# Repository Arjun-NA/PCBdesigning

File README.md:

# PCBdesigning

This is a repository of PCB designs

Currently the following

  1. [8x8 LED matrix control board](led%20matrix%20adapter%208x8%20rgb)
  2. [Breaker board for TLC 5951](/breaker%20board%20for%20tlc5951/)

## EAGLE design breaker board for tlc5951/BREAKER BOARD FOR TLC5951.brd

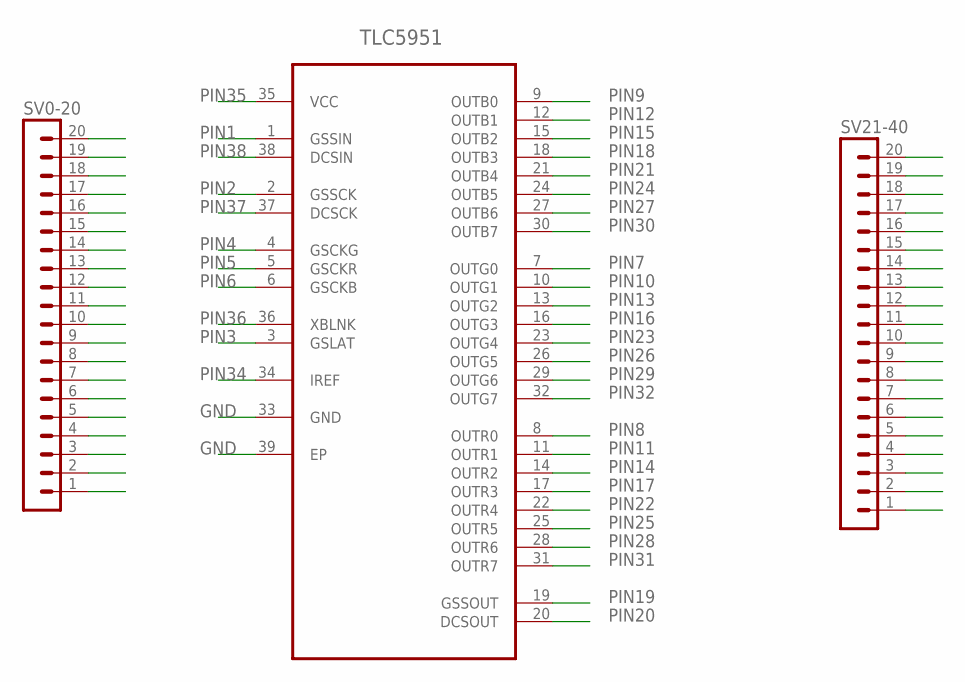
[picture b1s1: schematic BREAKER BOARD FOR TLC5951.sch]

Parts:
SV0-20, SV21-40: MA20-1
TLC5951: TLC5951DAP; SOP65P810X120-39N

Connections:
PIN1: SV0-20.1, TLC5951.1 (GSSIN)
PIN2: SV0-20.2, TLC5951.2 (GSSCK)
PIN3: SV0-20.3, TLC5951.3 (GSLAT)
PIN4: SV0-20.4, TLC5951.4 (GSCKG)
PIN5: SV0-20.5, TLC5951.5 (GSCKR)
PIN6: SV0-20.6, TLC5951.6 (GSCKB)
PIN7: SV0-20.7, TLC5951.7 (OUTG0)
PIN8: SV0-20.8, TLC5951.8 (OUTR0)
PIN9: SV0-20.9, TLC5951.9 (OUTB0)
PIN10: SV0-20.10, TLC5951.10 (OUTG1)
PIN11: SV0-20.11, TLC5951.11 (OUTR1)
PIN12: SV0-20.12, TLC5951.12 (OUTB1)
PIN13: SV0-20.13, TLC5951.13 (OUTG2)
PIN14: SV0-20.14, TLC5951.14 (OUTR2)
PIN15: SV0-20.15, TLC5951.15 (OUTB2)
PIN16: SV0-20.16, TLC5951.16 (OUTG3)
PIN17: SV0-20.17, TLC5951.17 (OUTR3)
PIN18: SV0-20.18, TLC5951.18 (OUTB3)
PIN19: SV0-20.19, TLC5951.19 (GSSOUT)
PIN20: SV21-40.19, TLC5951.20 (DCSOUT)
PIN21: SV21-40.18, TLC5951.21 (OUTB4)
PIN22: SV21-40.17, TLC5951.22 (OUTR4)
PIN23: SV21-40.16, TLC5951.23 (OUTG4)
PIN24: SV21-40.15, TLC5951.24 (OUTB5)
PIN25: SV21-40.14, TLC5951.25 (OUTR5)
PIN26: SV21-40.13, TLC5951.26 (OUTG5)
PIN27: SV21-40.12, TLC5951.27 (OUTB6)
PIN28: SV21-40.11, TLC5951.28 (OUTR6)
PIN29: SV21-40.10, TLC5951.29 (OUTG6)
PIN30: SV21-40.9, TLC5951.30 (OUTB7)
PIN31: SV21-40.8, TLC5951.31 (OUTR7)
PIN32: SV21-40.7, TLC5951.32 (OUTG7)
PIN34: SV21-40.5, TLC5951.34 (IREF)
PIN35: SV21-40.4, TLC5951.35 (VCC)
PIN36: SV21-40.3, TLC5951.36 (XBLNK)
PIN37: SV21-40.2, TLC5951.37 (DCSCK)
PIN38: SV21-40.1, TLC5951.38 (DCSIN)
PIN40: SV21-40.20

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
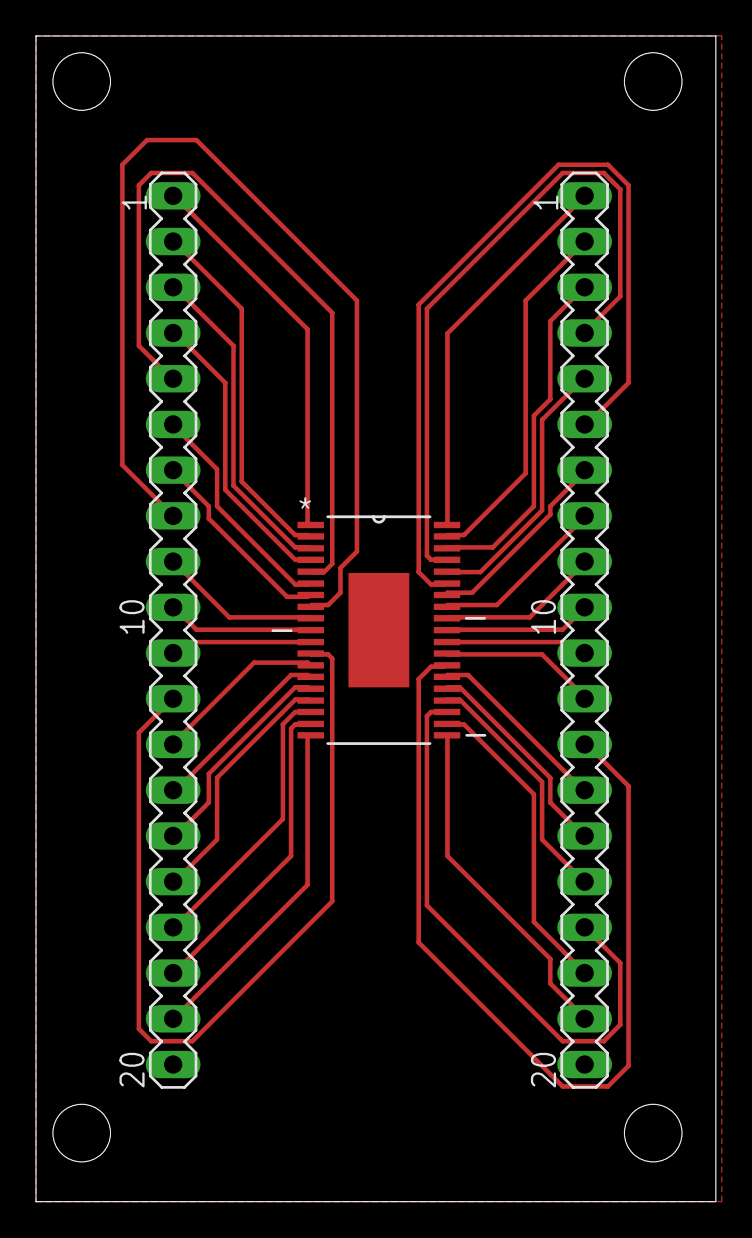
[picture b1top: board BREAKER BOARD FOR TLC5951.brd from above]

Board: 2 copper layers, 37.8 x 64.8 mm, 3 parts (0 on the bottom side), 38 nets.

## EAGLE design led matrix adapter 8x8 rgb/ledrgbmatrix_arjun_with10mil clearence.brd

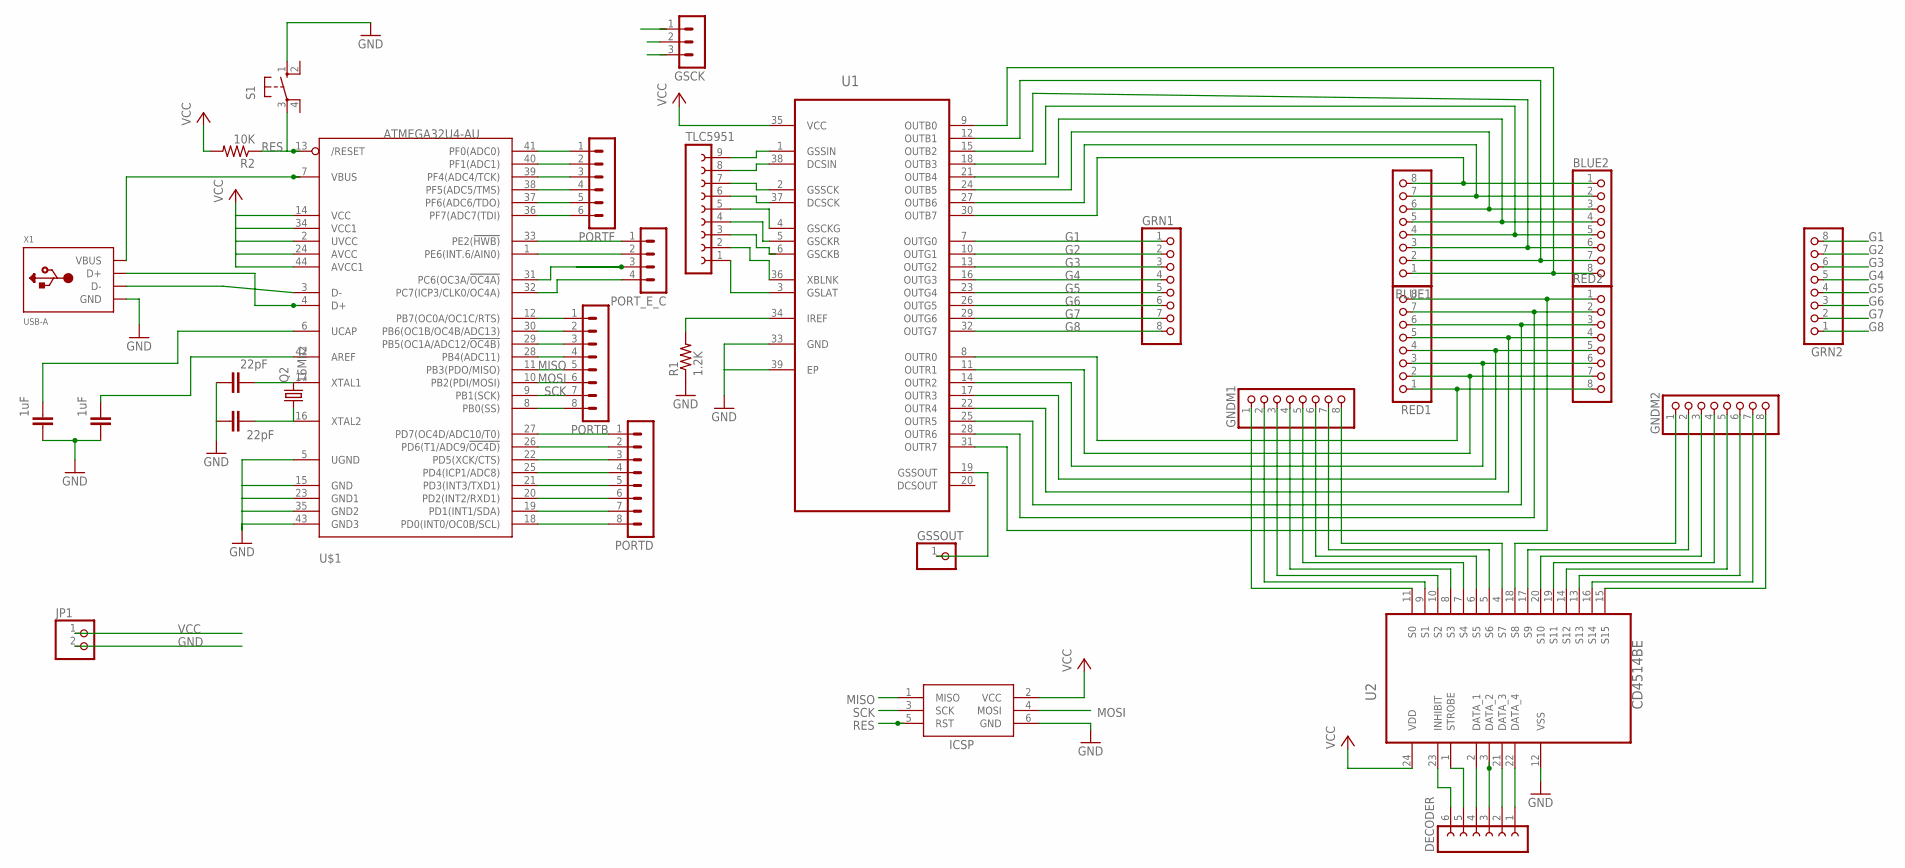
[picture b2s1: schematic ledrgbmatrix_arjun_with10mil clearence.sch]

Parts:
BLUE1, BLUE2: PINHD-1X8BIG; 1X08-BIG
C1, C2: 1uF; C2.5-2
C3, C4: 22pF; C2.5-2
DECODER: FE06-1; FE06
GNDM1, GNDM2: PINHD-1X8BIG; 1X08-BIG
GRN1, GRN2: PINHD-1X8BIG; 1X08-BIG
GSCK: MA03-1
GSSOUT: PINHD-1X1; 1X01
ICSP: AVRISP-6; AVRISP
JP1: PINHD-1X2; 1X02
PORTB: MA08-1
PORTD: MA08-1
PORTF: MA06-1
PORT_E_C: MA04-1
Q2: 16Mhz; HC49U-V
R1: 1.2K; 0207/12
R2: 10K; 0207/12
RED1, RED2: PINHD-1X8BIG; 1X08-BIG
S1: 10-XX; B3F-10XX
TLC5951: FE09-1; FE09
U1: TLC5951DAP; SOP65P810X120-39N
U2: CD4514BE; DIP254P1080X508-24
U$1: ATMEGA32U4-AU; TQFP44
X1: USB-A; MOLEX_480371000

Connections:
AREF: C1.2, U$1.42 (AREF)
B1: BLUE1.1, BLUE2.8, U1.9 (OUTB0)
B2: BLUE1.2, BLUE2.7, U1.12 (OUTB1)
B3: BLUE1.3, BLUE2.6, U1.15 (OUTB2)
B4: BLUE1.4, BLUE2.5, U1.18 (OUTB3)
B5: BLUE1.5, BLUE2.4, U1.21 (OUTB4)
B6: BLUE1.6, BLUE2.3, U1.24 (OUTB5)
B7: BLUE1.7, BLUE2.2, U1.27 (OUTB6)
B8: BLUE1.8, BLUE2.1, U1.30 (OUTB7)
C0: GNDM1.1, U2.11 (S0)
C1: GNDM1.2, U2.9 (S1)
C2: GNDM1.3, U2.10 (S2)
C3: GNDM1.4, U2.8 (S3)
C4: GNDM1.5, U2.7 (S4)
C5: GNDM1.6, U2.6 (S5)
C6: GNDM1.7, U2.5 (S6)
C7: GNDM1.8, U2.4 (S7)
C8: GNDM2.1, U2.18 (S8)
C9: GNDM2.2, U2.17 (S9)
C10: GNDM2.3, U2.20 (S10)
C11: GNDM2.4, U2.19 (S11)
C12: GNDM2.5, U2.14 (S12)
C13: GNDM2.6, U2.13 (S13)
C14: GNDM2.7, U2.16 (S14)
C15: GNDM2.8, U2.15 (S15)
D1: DECODER.4, U2.2 (DATA_1)
D2: DECODER.3, U2.3 (DATA_2)
D3: DECODER.2, U2.21 (DATA_3)
D4: DECODER.1, U2.22 (DATA_4)
D+: U$1.4 (D+), X1.3 (D+)
D-: U$1.3 (D-), X1.2 (D-)
DCSCK: TLC5951.6, U1.37 (DCSCK)
DSCIN: TLC5951.8, U1.38 (DCSIN)
G1: GRN1.1, GRN2.8, U1.7 (OUTG0)
G2: GRN1.2, GRN2.7, U1.10 (OUTG1)
G3: GRN1.3, GRN2.6, U1.13 (OUTG2)
G4: GRN1.4, GRN2.5, U1.16 (OUTG3)
G5: GRN1.5, GRN2.4, U1.23 (OUTG4)
G6: GRN1.6, GRN2.3, U1.26 (OUTG5)
G7: GRN1.7, GRN2.2, U1.29 (OUTG6)
G8: GRN1.8, GRN2.1, U1.32 (OUTG7)
GND: C1.1, C2.1, C3.1, C4.1, ICSP.6 (GND), JP1.2, R1.1, S1.1 (S), U1.33 (GND), U1.39 (EP), U2.12 (VSS), U$1.5 (UGND), U$1.15 (GND), U$1.23 (GND1), U$1.35 (GND2), U$1.43 (GND3), X1.4 (GND)
GSCKB: TLC5951.3, U1.6 (GSCKB)
GSCKG: TLC5951.5, U1.4 (GSCKG)
GSCKR: TLC5951.4, U1.5 (GSCKR)
GSLAT: TLC5951.1, U1.3 (GSLAT)
GSSCK: GSCK.2, TLC5951.7, U1.2 (GSSCK)
GSSIN: TLC5951.9, U1.1 (GSSIN)
GSSOUT: GSSOUT.1, U1.19 (GSSOUT)
INHIBIT: DECODER.6, U2.23 (INHIBIT)
IREF: R1.2, U1.34 (IREF)
MISO: ICSP.1 (MISO), PORTB.5, U$1.11 (PB3(PDO/MISO))
MOSI: ICSP.4 (MOSI), PORTB.6, U$1.10 (PB2(PDI/MOSI))
PB0: PORTB.8, U$1.8 (PB0(SS))
PB4: PORTB.4, U$1.28 (PB4(ADC11))
PB5: PORTB.3, U$1.29 (PB5(OC1A/ADC12/!OC4B))
PB6: PORTB.2, U$1.30 (PB6(OC1B/OC4B/ADC13))
PB7: PORTB.1, U$1.12 (PB7(OC0A/OC1C/RTS))
PC6: PORT_E_C.3, U$1.31 (PC6(OC3A/!OC4A))
PC7: PORT_E_C.4, U$1.32 (PC7(ICP3/CLK0/OC4A))
PD0: PORTD.8, U$1.18 (PD0(INT0/OC0B/SCL))
PD1: PORTD.7, U$1.19 (PD1(INT1/SDA))
PD2: PORTD.6, U$1.20 (PD2(INT2/RXD1))
PD3: PORTD.5, U$1.21 (PD3(INT3/TXD1))
PD4: PORTD.4, U$1.25 (PD4(ICP1/ADC8))
PD5: PORTD.3, U$1.22 (PD5(XCK/CTS))
PD6: PORTD.2, U$1.26 (PD6(T1/ADC9/!OC4D))
PD7: PORTD.1, U$1.27 (PD7(OC4D/ADC10/T0))
PE2: PORT_E_C.1, U$1.33 (PE2(!HWB))
PE6: PORT_E_C.2, U$1.1 (PE6(INT.6/AIN0))
PF0: PORTF.1, U$1.41 (PF0(ADC0))
PF1: PORTF.2, U$1.40 (PF1(ADC1))
PF4: PORTF.3, U$1.39 (PF4(ADC4/TCK))
PF5: PORTF.4, U$1.38 (PF5(ADC5/TMS))
PF6: PORTF.5, U$1.37 (PF6(ADC6/TDO))
PF7: PORTF.6, U$1.36 (PF7(ADC7(TDI))
R1: RED1.1, RED2.8, U1.8 (OUTR0)
R2: RED1.2, RED2.7, U1.11 (OUTR1)
R3: RED1.3, RED2.6, U1.14 (OUTR2)
R4: RED1.4, RED2.5, U1.17 (OUTR3)
R5: RED1.5, RED2.4, U1.22 (OUTR4)
R6: RED1.6, RED2.3, U1.25 (OUTR5)
R7: RED1.7, RED2.2, U1.28 (OUTR6)
R8: RED1.8, RED2.1, U1.31 (OUTR7)
RES: ICSP.5 (RST), R2.1, S1.3, U$1.13 (/RESET)
SCK: ICSP.3 (SCK), PORTB.7, U$1.9 (PB1(SCK))
STROBE: DECODER.5, U2.1 (STROBE)
UCAP: C2.2, U$1.6 (UCAP)
VBUS: U$1.7 (VBUS), X1.1 (VBUS)
VCC: ICSP.2 (VCC), JP1.1, R2.2, U1.35 (VCC), U2.24 (VDD), U$1.2 (UVCC), U$1.14 (VCC), U$1.24 (AVCC), U$1.34 (VCC1), U$1.44 (AVCC1)
XBLINK: TLC5951.2, U1.36 (XBLNK)
XTAL1: C3.2, Q2.2, U$1.17 (XTAL1)
XTAL2: C4.2, Q2.1, U$1.16 (XTAL2)

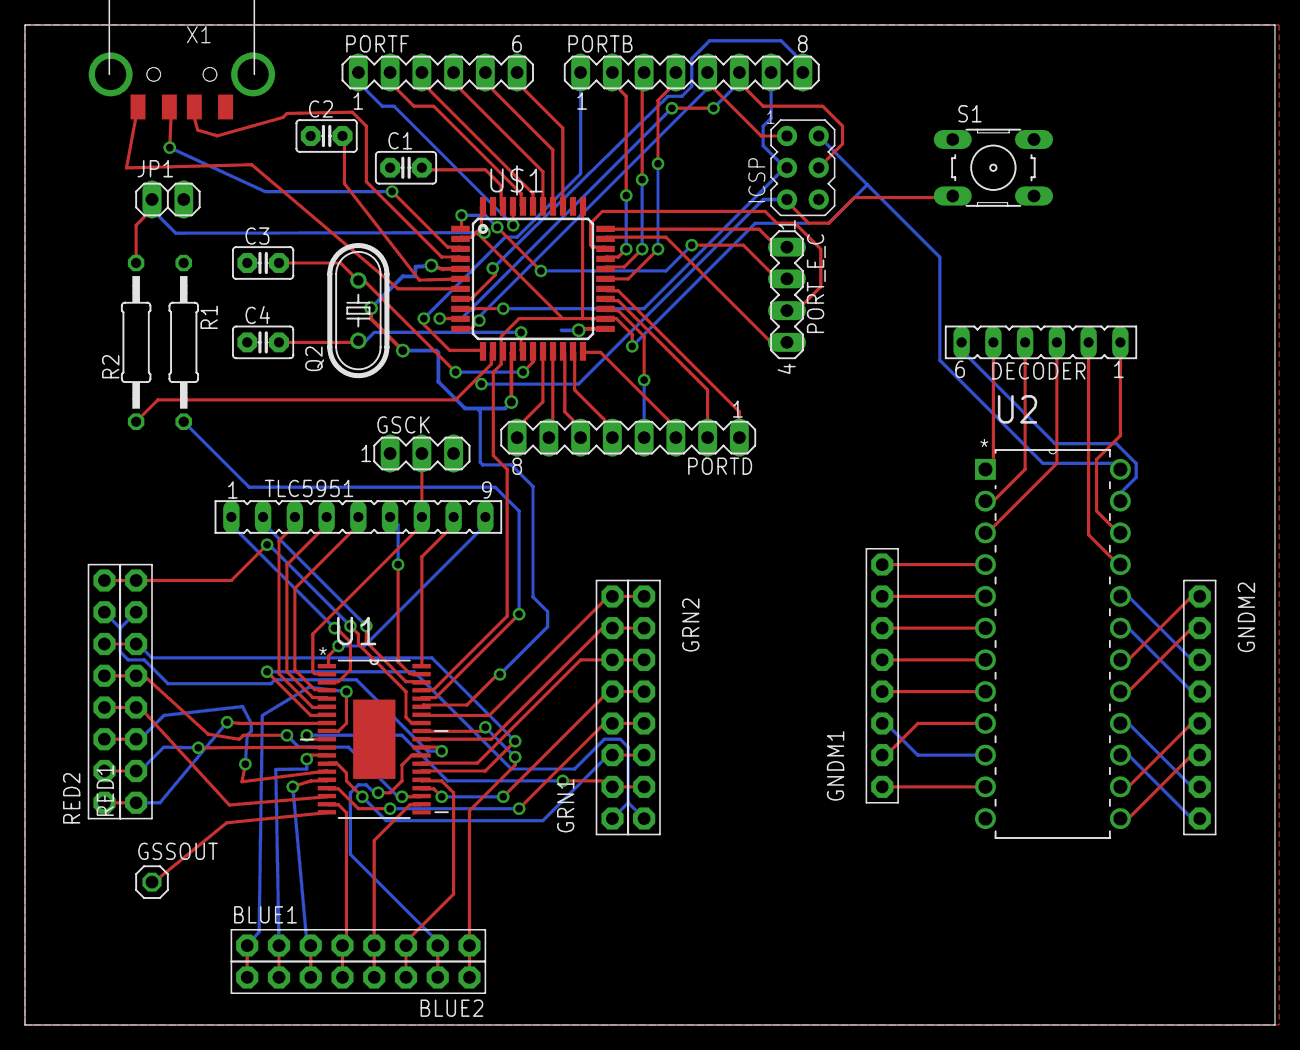
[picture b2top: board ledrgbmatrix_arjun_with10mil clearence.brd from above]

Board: 2 copper layers, 100.0 x 80.0 mm, 30 parts (0 on the bottom side), 93 nets.
